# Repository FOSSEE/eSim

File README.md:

<h1 align="center">eSim — Electronic Circuit Simulation</h1>

<p align="center">
  <strong>An Open-Source EDA Tool for Circuit Design, Simulation, Analysis & PCB Design</strong><br/>
  <em>Developed by <a href="https://www.fossee.in/">FOSSEE Team</a> at <a href="https://www.iitb.ac.in/">IIT Bombay</a></em>
</p>

<p align="center">

</p>

<p align="center">

</p>

<p align="center">
  <a href="#-features">Features</a> •
  <a href="#%EF%B8%8F-architecture">Architecture</a> •
  <a href="#-installation">Installation</a> •
  <a href="#-project-structure">Project Structure</a> •
  <a href="#-tech-stack">Tech Stack</a> •
  <a href="#-contributing">Contributing</a> •
  <a href="#-license">License</a>
</p>

---

## 📖 About

**eSim** is a free and open-source EDA (Electronic Design Automation) tool for circuit design, simulation, analysis, and PCB design. It is an integrated tool built using open-source software such as **KiCad**, **Ngspice**, **GHDL**, and **Makerchip**, providing a seamless workflow from schematic capture to simulation results.

eSim is designed for electronics engineers, students, educators, and hobbyists who want a powerful yet cost-free alternative to proprietary EDA tools. It supports analog, digital, and **mixed-signal simulations**, including microcontroller integration.

<p align="center">
  <b>📥 Download:</b> <a href="https://esim.fossee.in/downloads">v2.5 Release</a> &nbsp;&nbsp;|&nbsp;&nbsp; 
  <b>📄 Manual:</b> <a href="https://static.fossee.in/esim/manuals/eSim_Manual_2.5.pdf">PDF Guide</a> &nbsp;&nbsp;|&nbsp;&nbsp; 
  <b>📚 Docs:</b> <a href="https://esim.readthedocs.io/en/latest/">ReadTheDocs</a>
</p>

---

## ✨ Features

| Category | Feature | Description |
|:---------|:--------|:------------|
| • **Design** | Schematic Capture | Draw circuit schematics using KiCad's schematic editor with eSim's custom symbol libraries |
| • **Conversion** | KiCad to Ngspice | Convert KiCad schematics to Ngspice-compatible netlists for simulation |
| • **Simulation** | Ngspice Engine | Run DC, AC, Transient, and other SPICE analyses with real-time interactive plots |
| • **Analysis** | Waveform Plotting | Visualize simulation results with matplotlib-based Python plots and Ngspice native plots |
| • **Model Editor** | Device Models | Create and edit SPICE device models (Diodes, BJTs, MOSFETs, JFETs, IGBTs, etc.) |
| • **Subcircuits** | Subcircuit Builder | Build, manage, and upload reusable subcircuit blocks |
| • **Mixed-Signal** | NGHDL Integration | Interface VHDL digital models (via GHDL) with analog Ngspice simulations |
| • **Verilog** | Makerchip + NgVeri | Use Makerchip IDE for Verilog/TL-Verilog design and convert to Ngspice models |
| • **PCB** | Layout Design | Design PCB layouts using KiCad's PCB editor with eSim's footprint libraries |
| • **Converters** | Schematic Import | Convert PSpice and LTSpice schematics/libraries to KiCad-compatible formats |
| • **Modelica** | Ngspice-to-Modelica | Convert Ngspice netlists to Modelica models for OpenModelica simulation |
| • **SKY130 PDK** | SkyWater 130nm | Support for SkyWater SKY130 open-source Process Design Kit |
| • **IHP PDK** | IHP OpenPDK | Integration with IHP SG13G2 open-source PDK for SiGe BiCMOS |
| • **OpenROAD** | Netlist-to-ASIC | Automated digital ASIC design (Synthesis, placement, routing, layout generation) from Verilog RTL to GDSII layout|

---

## 🏗️ Architecture

### High-Level System Architecture

```mermaid
graph TB
    %% Styling
    classDef ui fill:#2A3F54,stroke:#1ABB9C,stroke-width:2px,color:#fff
    classDef core fill:#3E536C,stroke:#3498DB,stroke-width:2px,color:#fff
    classDef engine fill:#1F2D3D,stroke:#E74C3C,stroke-width:2px,color:#fff
    classDef data fill:#E9F0F5,stroke:#95A5A6,stroke-width:1px,color:#333
    
    subgraph UI ["User Interface (PyQt6)"]
        A[Application Main Window]:::ui
        PE[Project Explorer]:::ui
        DA[Dock Area Workspace]:::ui
        TE[Time Explorer]:::ui
        CON[Console Widget]:::ui
        
        A --> PE & DA & TE & CON
    end

    subgraph CORE ["Core Python Modules"]
        K2N[KiCad-to-Ngspice]:::core
        SIM[Ngspice Simulator]:::core
        PLT[Matplotlib Plotter]:::core
        ME[Model Editor]:::core
        SC[Subcircuit Builder]:::core
        
        DA --> K2N & SIM & ME & SC
    end

    subgraph INTEGRATION ["Mixed-Signal & External APIs"]
        NGHDL[NGHDL Interface]:::core
        MKR[Makerchip/NgVeri]:::core
        MOD[Modelica Converter]:::core
        CONV[PSpice/LTSpice Converter]:::core
        
        DA --> NGHDL & MKR & MOD & CONV
    end

    subgraph ENGINES ["Simulation & EDA Engines"]
        KICAD[KiCad Eeschema]:::engine
        PCB[KiCad Pcbnew]:::engine
        NGSPICE[Ngspice Backend]:::engine
        GHDL[GHDL Simulator]:::engine
        VER[Verilator]:::engine
        OM[OpenModelica]:::engine
    end

    %% Data Flow
    XML[(Netlist / XML)]:::data
    RAW[(Raw Data / txt)]:::data
    VHDL[(VHDL Files)]:::data
    
    K2N -- Generates --> XML
    XML -- Consumed by --> NGSPICE
    SIM -- Triggers --> NGSPICE
    NGSPICE -- Outputs --> RAW
    RAW -- Parsed by --> PLT
    
    NGHDL -- Compiles --> VHDL
    VHDL -- Simulated by --> GHDL
    GHDL -- Co-simulates --> NGSPICE
    
    MKR -- Verilog/TL-V --> VER
    
    KICAD -- Schematic --> K2N
    KICAD -- Netlist --> PCB
```

*For detailed simulation workflows, sub-system operations, and system flowcharts, please refer to our [Architecture & Workflows Guide](ARCHITECTURE.md).*

---

## 📂 Project Structure

### Root Directory

| Path | Type | Description |
|:-----|:-----|:------------|
| `src/` | 📁 Directory | **Core application source code** — all Python modules for the eSim GUI and backend |
| `library/` | 📁 Directory | **Component libraries** — device models, KiCad symbols, subcircuits, and PDK data |
| `nghdl/` | 📁 Directory | **NGHDL module** — Ngspice-GHDL interface for mixed-signal VHDL simulation |
| `Examples/` | 📁 Directory | **42 example projects** — ready-to-simulate circuits (RC, BJT, Op-Amp, Mixed-Signal, etc.) |
| `images/` | 📁 Directory | **UI assets** — application icons, toolbar images, logos, and splash screen |
| `scripts/` | 📁 Directory | **Launch & setup scripts** — shell scripts for Linux installation and launching |
| `docs/` | 📁 Directory | **Sphinx documentation** — RST files for ReadTheDocs auto-generated developer docs |
| `code/` | 📁 Directory | **Sphinx autodoc config** — mirrors `src/` structure for API documentation generation |
| `flatpak/` | 📁 Directory | **Flatpak packaging** — manifest and wrapper scripts for universal Linux distribution |
| `appimage/` | 📁 Directory | **AppImage packaging** — build scripts for portable Linux AppImage bundles |
| `docker-launcher/` | 📁 Directory | **Docker support** — Dockerfile, launcher script, and CI workflows for containerized builds |
| `snap/` | 📁 Directory | **Snap packaging** — `snapcraft.yaml` for building Snap packages |
| `ihp/` | 📁 Directory | **IHP PDK integration** — install script for IHP SG13G2 open-source SiGe BiCMOS PDK |
| `orfs/` | 📁 Directory | **OpenROAD integration** — install & setup scripts for ORFS (RTL-to-GDSII ASIC design & layout) |
| `patches/` | 📁 Directory | **Source patches** — patch files for modifying Ngspice/GHDL behavior in sandboxed environments |
| `.github/` | 📁 Directory | **GitHub config** — issue templates, PR templates, and CI/CD workflow definitions |
| `setup.py` | 📄 File | Python package configuration for pip installation |
| `requirements.txt` | 📄 File | Python dependency list (PyQt6, matplotlib, numpy, scipy, etc.) |
| `conf.py` | 📄 File | Sphinx documentation configuration |
| `VERSION` | 📄 File | Current version identifier (`2.5`) |
| `INSTALL` | 📄 File | Detailed multi-platform installation instructions |
| `LICENSE` | 📄 File | GNU General Public License v3.0 |

### Source Code (`src/`) — Detailed Module Breakdown

```
src/
├── frontEnd/               # GUI & Main Application
│   ├── Application.py      # Main window, toolbar setup, menu actions (960 lines)
│   ├── DockArea.py          # Tabbed dock workspace for editors/simulators (24K)
│   ├── ProjectExplorer.py   # File tree browser for project navigation (20K)
│   ├── TimeExplorer.py      # Project snapshot/version management (8K)
│   ├── TerminalUi.py        # Embedded terminal widget (5K)
│   └── Workspace.py         # Workspace selection dialog (6K)
│
├── kicadtoNgspice/          # KiCad-to-Ngspice Conversion Engine
│   ├── KicadtoNgspice.py    # Main conversion controller & UI (41K)
│   ├── Convert.py           # Netlist parsing and SPICE generation (40K)
│   ├── Analysis.py          # Analysis type configuration (DC, AC, Transient) (32K)
│   ├── DeviceModel.py       # Device model parameter handling (56K)
│   ├── Source.py             # Source component configuration (15K)
│   ├── Processing.py         # Netlist processing pipeline (26K)
│   ├── SubcircuitTab.py      # Subcircuit selection in converter (9K)
│   ├── Microcontroller.py    # Microcontroller model support (10K)
│   ├── Model.py              # Model file handling (6K)
│   └── TrackWidget.py        # UI tracking widget (1K)
│
├── ngspiceSimulation/       # Simulation Engine & Plotting
│   ├── NgspiceWidget.py     # Ngspice process management & execution (16K)
│   ├── plot_window.py       # matplotlib-based waveform plotter (66K)
│   ├── plotting_widgets.py  # Custom plot controls and widgets (8K)
│   └── data_extraction.py   # Simulation data file parser (11K)
│
├── modelEditor/             # SPICE Model Editor
│   └── ModelEditor.py       # GUI for creating/editing device models (33K)
│
├── subcircuit/              # Subcircuit Management
│   ├── Subcircuit.py        # Subcircuit manager main window (3K)
│   ├── newSub.py            # Create new subcircuit (3K)
│   ├── openSub.py           # Open existing subcircuit (1K)
│   ├── uploadSub.py         # Upload subcircuit to library (4K)
│   └── convertSub.py        # Subcircuit format conversion (2K)
│
├── maker/                   # Makerchip & NgVeri Integration
│   ├── Maker.py             # Makerchip IDE integration (23K)
│   ├── NgVeri.py            # Verilog-to-Ngspice model generator (17K)
│   ├── ModelGeneration.py   # Auto model generation pipeline (48K)
│   ├── createkicad.py       # KiCad symbol creation for models (14K)
│   ├── makerchip.py         # Makerchip cloud IDE connector (3K)
│   ├── netlist2rtl.py       # Netlist-to-Verilog conveter (4K)
│   ├── orfs.py              # eSim to ORFS connnector (7K)
│   └── Appconfig.py         # Maker-specific configuration (2K)
│
├── converter/               # Schematic Format Converters
│   ├── pspiceToKicad.py     # PSpice schematic importer (5K)
│   ├── ltspiceToKicad.py    # LTSpice schematic importer (6K)
│   ├── libConverter.py      # Library format converter (3K)
│   ├── LtspiceLibConverter.py # LTSpice library converter (4K)
│   ├── browseSchematic.py   # File browser for schematics (550B)
│   ├── LTSpiceToKiCadConverter/ # LTSpice conversion engine
│   └── schematic_converters/    # Additional schematic parsers
│
├── ngspicetoModelica/       # 📐 Ngspice-to-Modelica Converter
│   ├── NgspicetoModelica.py # Core conversion engine (54K)
│   └── ModelicaUI.py        # Modelica converter GUI (10K)
│
├── configuration/           # ⚙️ Application Configuration
│   └── Appconfig.py         # Global config, paths, process tracking (4K)
│
├── projManagement/          # 📋 Project Management
│   ├── Kicad.py             # KiCad integration (launch schematic/PCB editor) (9K)
│   ├── Validation.py        # Tool and file validation utilities (7K)
│   ├── Worker.py            # Background process/thread management (3K)
│   ├── newProject.py        # New project creation logic (5K)
│   └── openProject.py       # Open existing project logic (3K)
│
└── browser/                 # 📖 Help & Documentation
    ├── Welcome.py           # Welcome screen display (941B)
    └── UserManual.py        # User manual viewer (731B)
```

### Library Directory (`library/`) — Component Libraries

| Path | Description |
|:-----|:------------|
| `deviceModelLibrary/` | SPICE device models organized by type: Diode, BJT (Transistor), MOSFET (MOS), JFET, IGBT, LEDs, Switches, Transmission Lines, and user libraries |
| `kicadLibrary/` | KiCad schematic symbols (`eSim-symbols/`), footprint libraries (`kicad_eSim-Library/`), and project templates |
| `SubcircuitLibrary/` | Reusable subcircuit definitions for common circuit blocks |
| `modelParamXML/` | XML parameter definitions for device model editor forms |
| `ngspicetoModelica/` | Mapping files for Ngspice-to-Modelica component translation |
| `browser/` | HTML/resource files for the built-in help browser |
| `orfs/` | KLayout binaries & libraries (klayout-0.30.7) required for OpenROAD/ASIC layout visualization |
| `tlv/` | TL-Verilog support files for Makerchip integration |

### NGHDL Module (`nghdl/`) — Mixed-Signal Interface

| Path | Description |
|:-----|:------------|
| `src/ngspice_ghdl.py` | Core interface: manages VHDL upload, GHDL compilation, and Ngspice code model creation |
| `src/model_generation.py` | Generates C code models from VHDL port definitions for Ngspice |
| `src/createKicadLibrary.py` | Auto-generates KiCad symbols from VHDL entity definitions |
| `src/ghdlserver/` | GHDL foreign interface server for inter-process communication with Ngspice |
| `install-nghdl.sh` | Automated installer for NGHDL dependencies (GHDL, Verilator, Ngspice) |
| `Example/` | Example VHDL models and mixed-signal simulation projects |

---

## 🛠️ Tech Stack

| Layer | Technology | Purpose |
|:------|:-----------|:--------|
| **Language** |  | Core application logic |
| **GUI Framework** |  | Desktop GUI (windows, dialogs, toolbars, docks) |
| **Plotting** |  | Waveform visualization and data plotting |
| **Numerics** |   | Numerical computation and signal processing |
| **Schematic & PCB** |  | Schematic capture and PCB layout design |
| **SPICE Simulation** |  | Analog/mixed-signal circuit simulation engine |
| **VHDL Simulation** |  | VHDL analysis, compilation, and simulation |
| **Verilog** |  | Verilog HDL simulation and model generation |
| **HDL Cloud IDE** |  | Online Verilog/TL-Verilog IDE integration |
| **Modelica** |  | Multi-domain modeling and simulation |
| **PDK** |  | SkyWater 130nm open-source process design kit |
| **Packaging** |   | Cross-distribution Linux packaging & containers |
| **Documentation** |   | Auto-generated developer documentation |
| **CI/CD** |  | Automated builds, Docker images, and releases |

### Key Python Dependencies

| Package | Version | Purpose |
|:--------|:--------|:--------|
| `PyQt6` | ≥ 6.5.0 | GUI framework |
| `matplotlib` | 3.7.5 | Waveform plotting |
| `numpy` | 1.24.4 | Numerical computation |
| `scipy` | 1.10.1 | Scientific computing |
| `pillow` | 12.2.0 | Image processing |
| `hdlparse` | 1.0.4 | HDL file parsing |
| `watchdog` | 4.0.2 | File system monitoring |
| `pyparsing` | 3.1.4 | Parser building toolkit |

---

## 💻 Installation

### Supported Platforms

| Platform | Method | Status |
|:---------|:-------|:------:|
| **All Linux** (Fedora, Ubuntu, openSUSE, Arch, etc.) | Flatpak | ✅ Recommended |
| **Ubuntu** 22.04 / 23.04 / 24.04 LTS | Native Installer | ✅ Supported |
| **Windows** 8 / 10 / 11 | Windows Installer | ✅ Supported |
| **Docker** (any OS) | Docker Container | ✅ Supported |

### 🐧 Linux — Flatpak (Recommended for all distributions)

```bash
# 1. Install Flatpak (if not already installed)
# Fedora:    sudo dnf install flatpak
# Ubuntu:    sudo apt install flatpak
# openSUSE:  sudo zypper install flatpak
# Arch:      sudo pacman -S flatpak

# 2. Add Flathub repository
flatpak remote-add --if-not-exists flathub https://dl.flathub.org/repo/flathub.flatpakrepo

# 3. Install eSim
flatpak install flathub org.fossee.eSim

# 4. Run eSim
flatpak run org.fossee.eSim
```

> **⚠️ Flatpak Limitations:** NGHDL, Makerchip, and SKY130 PDK are not included in the Flatpak build. For full mixed-signal support, use the Ubuntu native installer.

### 🐧 Ubuntu — Native Installer

```bash
# 1. Download and extract eSim
unzip eSim-2.5.zip
cd eSim-2.5

# 2. Install eSim with all dependencies
chmod +x install-eSim.sh
./install-eSim.sh --install

# 3. Run eSim
esim
# Or double-click the eSim desktop icon
```

### 🪟 Windows

1. Download the eSim installer from [esim.fossee.in/downloads](https://esim.fossee.in/downloads)
2. Disable antivirus temporarily (if required)
3. **Important:** Remove MinGW/MSYS from the PATH environment variable if previously installed
4. Run the installer and follow the on-screen instructions
5. Launch eSim from the Start Menu or desktop shortcut

### 🐋 Docker

Refer to the [Docker Launcher README](docker-launcher/README.md) for instructions on running eSim in a containerized environment.

### 📦 Build from Source (Flatpak)

```bash
cd eSim
flatpak-builder build flatpak/org.fossee.eSim.yml --install --user
```

> 📖 For comprehensive installation instructions, see the [INSTALL](INSTALL) file.

---

## 🔄 CI/CD & Packaging

| Workflow | File | Purpose |
|:---------|:-----|:--------|
| Docker Image Build | `.github/workflows/docker-image.yml` | Builds and publishes the eSim Docker image |
| Docker Launcher Build | `.github/workflows/docker-launcher-build.yml` | Builds the cross-platform Python launcher |
| Ubuntu Release | `.github/workflows/release_ubuntu.yml` | Automated Ubuntu `.deb` package builds |

| Packaging Format | Directory | Description |
|:-----------------|:----------|:------------|
| Flatpak | `flatpak/` | Universal Linux package via Flathub |
| AppImage | `appimage/` | Portable single-file Linux executable |
| Snap | `snap/` | Ubuntu Snap Store package |
| Docker | `docker-launcher/` | Containerized distribution with GUI forwarding |

---

## 📋 Example Projects

eSim ships with **42 ready-to-simulate example projects** in the `Examples/` directory:

<details>
<summary><b>📂 Click to expand full example list</b></summary>

| # | Category | Example | Description |
|:-:|:---------|:--------|:------------|
| 1 | 🔌 Basic | `RC` | RC circuit transient analysis |
| 2 | 🔌 Basic | `RL` | RL circuit transient analysis |
| 3 | 🔌 Basic | `RLC` | RLC circuit resonance analysis |
| 4 | 🔌 Basic | `Series_Resonance` | Series RLC resonance |
| 5 | 🔌 Basic | `Parallel_Resonance` | Parallel RLC resonance |
| 6 | 💡 Diodes | `Diode_characteristics` | Diode I-V characteristics |
| 7 | 💡 Diodes | `Halfwave_Rectifier` | Half-wave rectifier circuit |
| 8 | 💡 Diodes | `Fullwavebridgerectifier` | Full-wave bridge rectifier |
| 9 | 💡 Diodes | `Clippercircuit` | Diode clipper circuit |
| 10 | 💡 Diodes | `Clampercircuit` | Diode clamper circuit |
| 11 | 💡 Diodes | `Zener_Characteristic` | Zener diode characteristics |
| 12 | 🔋 BJT | `BJT_CE_config` | BJT common-emitter configuration |
| 13 | 🔋 BJT | `BJT_CB_config` | BJT common-base configuration |
| 14 | 🔋 BJT | `BJT_amplifier` | BJT amplifier circuit |
| 15 | 🔋 BJT | `BJT_Biascircuit` | BJT bias circuit design |
| 16 | 🔋 BJT | `BJT_Frequency_Response` | BJT frequency response analysis |
| 17 | 📟 FET | `FET_Characteristic` | FET output characteristics |
| 18 | 📟 FET | `FET_Amplifier` | FET amplifier circuit |
| 19 | 📟 FET | `FrequencyResponse_JFET` | JFET frequency response |
| 20 | 🎛️ Op-Amp | `InvertingAmplifier` | Op-amp inverting amplifier (LM741) |
| 21 | 🎛️ Op-Amp | `Differentiator` | Op-amp differentiator circuit |
| 22 | 🎛️ Op-Amp | `Integrator_LM_741` | Op-amp integrator |
| 23 | 🎛️ Op-Amp | `Precision_Rectifiers_using_LM741` | Precision rectifier circuits |
| 24 | 🔲 Digital | `BasicGates` | Basic logic gates |
| 25 | 🔲 Digital | `Half_Adder` | Half-adder circuit |
| 26 | 🔲 Digital | `FullAdder` | Full-adder circuit |
| 27 | 🔲 Digital | `JK_Flipflop` | JK flip-flop circuit |
| 28 | 🔲 Digital | `4_bit_JK_ff` | 4-bit JK flip-flop counter |
| 29 | 🔲 Digital | `CMOS_NAND_Gate` | CMOS NAND gate |
| 30 | 🔲 Digital | `Analysis_Of_Digital_IC` | Digital IC analysis |
| 31 | ⏱️ Timers | `Astable555` | 555 timer astable mode |
| 32 | ⏱️ Timers | `Monostable555` | 555 timer monostable mode |
| 33 | 🔁 SCR | `HalfwaveRectifier_SCR` | SCR half-wave rectifier |
| 34 | 🔁 SCR | `FullwaveRectifier_SCR` | SCR full-wave rectifier |
| 35 | 📡 Filters | `High_Pass_Filter` | High-pass filter design |
| 36 | 📡 Filters | `Low_Pass_Filter` | Low-pass filter design |
| 37 | ⚡ Regulators | `7805VoltageRegulator` | 7805 voltage regulator |
| 38 | ⚡ Regulators | `7812VoltageRegulator` | 7812 voltage regulator |
| 39 | 🌀 Oscillators | `UJT_Relaxation_Oscillator` | UJT relaxation oscillator |
| 40 | 🌀 Oscillators | `Phase_Locked_Loop` | PLL circuit |
| 41 | 🔀 Mixed-Signal | `Mixed_Signal` | Mixed analog-digital simulation (NGHDL) |
| 42 | 🔌 Power | `Transformer` | Transformer circuit analysis |

</details>

---

## 🤝 Contributing

We welcome contributions from the community! Whether it's bug fixes, new features, documentation improvements, or example circuits — every contribution matters.

### How to Contribute

```mermaid
flowchart LR
    A["🍴 Fork<br/>Repository"] --> B["🌿 Create<br/>Branch"]
    B --> C["💻 Make<br/>Changes"]
    C --> D["✅ Commit &<br/>Push"]
    D --> E["📬 Open<br/>Pull Request"]

    style A fill:#6c5ce7,color:#fff
    style B fill:#00b894,color:#fff
    style C fill:#0984e3,color:#fff
    style D fill:#fdcb6e,color:#333
    style E fill:#e17055,color:#fff
```

1. **Fork** the repository to your GitHub account
2. **Clone** your fork:
   ```bash
   git clone https://github.com/<your-username>/eSim.git
   ```
3. **Create a new branch** for your changes:
   ```bash
   git checkout -b feature/your-feature-name
   ```
4. **Make your changes** and commit with a descriptive message:
   ```bash
   git add <files>
   git commit -m "Fixes issue #<number> - Brief description of changes"
   ```
5. **Push** to your fork and **open a Pull Request**:
   ```bash
   git push origin feature/your-feature-name
   ```

> **📌 Guidelines:**
> - Each PR should reference an existing issue
> - One commit per pull request (squash if needed)
> - Follow [PEP 8](https://www.python.org/dev/peps/pep-0008/) code style
> - Include a commit body describing what you changed and why

For detailed contribution guidelines, see [CONTRIBUTING.md](CONTRIBUTING.md).

---

## 👥 Contributors

A huge thank you to all **149+ amazing people** who have contributed to eSim! 🎉

<table align="center" style="border:none;">
  <tr>
    <td align="center" width="250" style="border:none;">
      <a href="https://github.com/Eyantra698Sumanto" style="text-decoration:none;">
        <br/>
        <b>🥇 Sumanto Kar</b>
      </a><br/>
      <sub>Lead Maintainer · 320 commits</sub>
    </td>
    <td align="center" width="250" style="border:none;">
      <a href="https://github.com/rahulp13" style="text-decoration:none;">
        <br/>
        <b>🥈 Rahul Paknikar</b>
      </a><br/>
      <sub>265 commits</sub>
    </td>
    <td align="center" width="250" style="border:none;">
      <a href="https://github.com/fahim-oscad" style="text-decoration:none;">
        <br/>
        <b>🥉 Fahim Khan</b>
      </a><br/>
      <sub>244 commits</sub>
    </td>
  </tr>
</table>

<p align="center">
  
</p>

<p align="center"><em>149+ contributors and counting! <a href="https://github.com/fossee/esim/graphs/contributors">View all contributors →</a></em></p>

---

## 📞 Contact & Support

| Channel | Link |
|:--------|:-----|
| 📧 **Email** | [contact-esim@fossee.in](mailto:contact-esim@fossee.in) |
| 🌐 **Website** | [esim.fossee.in](https://esim.fossee.in/) |
| 💬 **Forum** | [forums.fossee.in](https://forums.fossee.in/) |
| 📞 **Contact Page** | [esim.fossee.in/contact-us](https://esim.fossee.in/contact-us) |
| 📄 **User Manual** | [eSim Manual v2.5 (PDF)](https://static.fossee.in/esim/manuals/eSim_Manual_2.5.pdf) |
| 📚 **Developer Docs** | [esim.readthedocs.io](https://esim.readthedocs.io/en/latest/) |

---

<p align="center">
  <strong>Built with ❤️ by the <a href="https://www.fossee.in/">FOSSEE Team</a> at <a href="https://www.iitb.ac.in/">IIT Bombay</a></strong>
</p>

<p align="center">
  
  &nbsp;&nbsp;&nbsp;&nbsp;
  
</p>

<p align="center">
  <sub>⭐ If you find eSim useful, consider giving it a star on GitHub!</sub>
</p>

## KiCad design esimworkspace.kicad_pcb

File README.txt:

# REF01 Precision Voltage Reference

REF01 is an 8-pin precision voltage reference IC. It provides a stable 10.0 V reference output with excellent temperature stability, low noise, and high accuracy. The output voltage can be adjusted by approximately ±3% using an external trim resistor. It is widely used in precision analog and measurement applications. :contentReference[oaicite:0]{index=0}

## Usage/Examples

Precision Data Acquisition Systems

Analog-to-Digital Converters (ADC)

Digital-to-Analog Converters (DAC)

Industrial Process Control

Precision Test and Measurement Instruments

Reference Voltage Sources

## Documentation

To know the details of REF01 IC please go through the documentation : https://www.analog.com/media/en/technical-documentation/data-sheets/REF01_02_03.pdf :contentReference[oaicite:1]{index=1}

## Comments/Notes

Please note this is a precision voltage reference IC intended for applications requiring a highly stable reference voltage. The device operates from an input supply of 12 V to 36 V and provides a fixed 10 V output with up to 10 mA load current. Proper supply bypassing and PCB layout are recommended to achieve optimum noise performance and stability. :contentReference[oaicite:2]{index=2}

## Contributer

Name: *Sanchi Ramteke*  
Email: *sanchiramteke2008@gmail.com*  
Year: 2026  
Position: Contributor

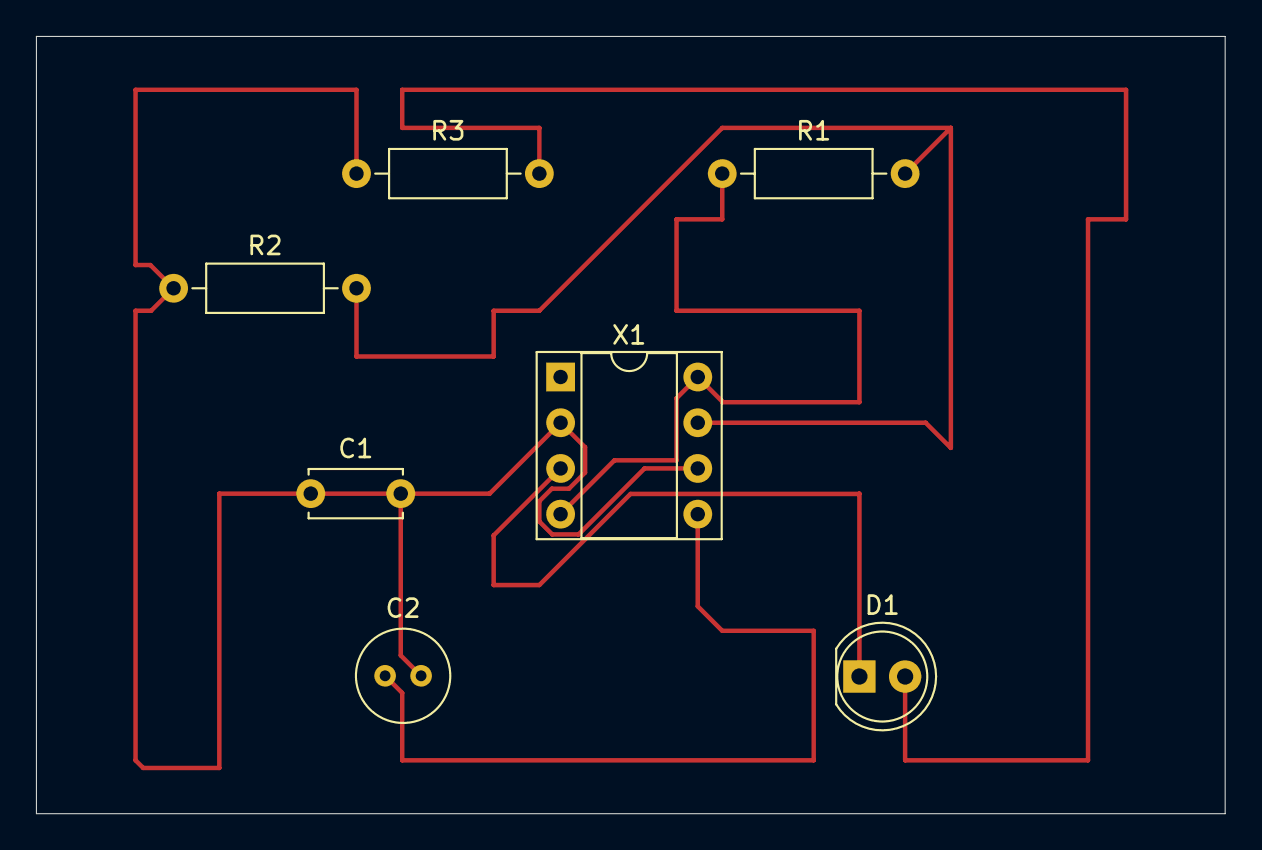
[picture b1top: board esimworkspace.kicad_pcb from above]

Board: 2 copper layers, 66.0 x 43.2 mm, 7 parts (0 on the bottom side), 6 nets.

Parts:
C1: capacitor; C_Disc_D5.0mm_W2.5mm_P5.00mm
C2: capacitor; C_Radial_D5.0mm_H7.0mm_P2.00mm
D1: LED; LED_D5.0mm
R1, R2, R3: resistor; R_Axial_DIN0207_L6.3mm_D2.5mm_P10.16mm_Horizontal
X1: NE555; DIP-8_W7.62mm_Socket

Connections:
GND: C1.1, C1.2, C2.2, R2.1, R3.1, X1.2 (TRIG), X1.6 (THRS)
unnamed: C2.1, X1.5 (CV)
unnamed: D1.1 (+), X1.3 (OUT)
unnamed: D1.2 (-), R3.2
unnamed: R1.1, X1.4 (RST), X1.8 (Vcc)
unnamed: R1.2, R2.2, X1.7 (DIS)

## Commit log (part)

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2026-06-13 SNx4HC03 is Quad 2-input NAND gate IC.
2026-06-13 SNx5452B is AND-OR-Invert gate IC.
2026-06-13 fix: replace exec_() with exec() in Chatbot.py for PyQt6 compatibility
2026-06-14 refactor(ui): embed individual tool manager into main tab
2026-06-14 fix(ui): remove redundant button linking to deleted function
2026-06-14 feat(ui): implement three-tab layout for individual tool manager
2026-06-14 refactor(ui): streamline interface constraints and restore minimal layout structure
2026-06-15 refactor: move platform-specific code to platform_util.py
2026-06-15 Fixed the missing PYTHON variable from gui_fixed.py
2026-06-16 fix: migrate frontEnd enums to PyQt6 and add standalone chatbot launcher for chatbot testing
2026-06-16 fix: fix remaining QTextCursor PyQt5 enums restored by merge conflict
2026-06-16 Some more refactoring
2026-06-17 cleanup(toolManager): delete dead shell scripts and orphaned bytecode
    check-packages-final.sh and update-dependency-final.sh had zero
    references in the entire repository — completely dead code.
    Deleted 4 orphaned .pyc files from __pycache__ that had no
    corresponding .py source (covered by existing *.pyc gitignore).
2026-06-17 feat(toolManager): create pm_platform.py — unified OS detection, subprocess, admin helpers
2026-06-17 refactor(toolManager): modular architecture with backends/ package, worker, and unified registry
    Break the 1434-line tool_manager_windows.py monolith into a clean
    backends/ package with adapter pattern for backward compatibility.
    === backends/ package (Phase 5) ===
    - base.py — Backend(ABC) with find_executable, install_package,
    download_file, extract_7z, run_installer, and shared run_cmd/which
    - windows/ — WindowsBackend wrapping Chocolatey (choco.py),
2026-06-18 feat: automate headless Ollama startup and model pulling
2026-06-19 feat(toolManager): LinuxBackend with package manager abstraction and tool file Linux branches
    Phase 6 & 7 — complete Linux backend infrastructure and cleanup:
    - backends/linux/ package (replaces flat linux.py):
    - pm.py — abstraction for apt, dnf, pacman, zypper, pkg, xbps
    - search.py — Linux executable discovery (PATH + /opt + snap/flatpak)
    - file_ops.py — tar, 7z, .sh/.run installer support
    - __init__.py — LinuxBackend class with run_bash_script() helper
2026-06-19 fix(toolManager): create tool_manager_linux.py CLI adapter and fix PyQt6 crash
    - Create tool_manager_linux.py — Linux CLI adapter mirroring
    tool_manager_windows.py but using LinuxBackend
    - Fix main.py lines 100 and 654 to select the correct backend
    script based on platform (linux vs windows)
    - Fix gui_fixed.py PyQt6 crash: QLineEdit.Password →
    QLineEdit.EchoMode.Password
2026-06-19 fix(linux): correct base_dir path resolution for backends/linux/ package
    When linux.py was a flat file, parent.parent resolved to toolManager/.
    After converting to a package (backends/linux/__init__.py), the path
    is one level deeper, so parent.parent.parent is needed.
2026-06-19 Add ORFS OpenROAD flow integration
2026-06-19 fix(toolManager): replace sudo password with pkexec and stream script output
    Three issues fixed:
    1. Script output now streams to GUI debug box in real time
    - run_bash_script() uses run_stream() instead of run_cmd()
    - Script stdout/stderr flows through to the CommandWorker pipe
    2. Removed manual sudo password collection (insecure, broken)
    - Deleted get_sudo_password(), self.sudo_password, needs_sudo flag
2026-06-19 fix(toolManager): cache sudo credential via sudo -S -v instead of pkexec
    Changes:
    - Remove pkexec from CommandWorker (caused 'Not authorized' errors,
    prompted for every command including check)
    - Restore sudo password prompt but only for credential caching
    - New _ensure_sudo_cache() collects password once, runs sudo -S -v
    to cache it, then discards password from memory
2026-06-19 refactor(toolManager): move sudo/lock logic into LinuxBackend, serialize bash scripts
    LinuxBackend (backends/linux/__init__.py):
    - sudo_is_cached() — check if credential is alive via sudo -n
    - ensure_sudo(password) — cache password via sudo -S -v
    - clean_package_locks() — remove stale dpkg/pacman/dnf/zypper locks
    - run_bash_script() — now serialized via threading.Lock and calls
    clean_package_locks() before every script execution, preventing
2026-06-19 Refactor platform detection and registry
2026-06-19 Enhance README with OpenROAD and ORFS details
    Added OpenROAD integration details and new files for netlist-to-ASIC design.
2026-06-19 Rename orfs-install-guide.md to README.md
2026-06-19 fix(toolManager): CLI adapter, sudo improvements, lock serialization, and path fixes
    - Add tool_manager_linux.py CLI adapter
    - Fix PyQt6 crash by inserting local path into sys.path
    - Fix base_dir path resolution for backends/linux/ package
    - Replace sudo password prompt with pkexec wrapper for GUI mode
    - Cache sudo credential via sudo -S -v instead of pkexec
    - Move sudo/lock logic (sudo_is_cached, ensure_sudo, clean_package_locks) into LinuxBackend
2026-06-19 Add deterministic netlist analysis pipeline for eSim AI Assistant
    Include:
    * netlist parsing improvements
    * circuit block detection
    * netlist summary generation
    * AI Assistant netlist understanding
    * related prompt refinements
2026-06-20 refactor(toolManager): compress 3,964 lines to 1,439 by merging tool files and deduplicating
2026-06-20 Renaming issue fixed to reduce diff noise
    Renaming fixed
2026-06-21 style(tool-manager): polish PyQt6 UI and fix dark theme inconsistencies
    This commit improves the Tool Manager UI layout and explicitly forces
    light-themed styling to fix visual bugs caused by OS-level dark mode bleeds,
    without altering any core installation or backend logic.
    UI Fixes & Improvements:
    - Wrap "Quick Setup" tab in a QScrollArea to prevent install buttons from
    being squished or hidden when the installation progress frame appears.
2026-06-21 Add deterministic NgSpice error analysis and root-cause detection pipeline
    Improve root-cause identification for NgSpice simulation failures
    - Add structured extraction of models, subcircuits and circuit facts
    - Support multiple simultaneous critical errors
    - Improve error ranking and causal relationship handling
    - Reduce hallucinated diagnostics through deterministic validation
    - Integrate analysis pipeline into chatbot workflow
2026-06-21 Added a backend file for linux and changes to the installation and uninstallation worker
2026-06-22 Move subcircuit files from SUBCKT to library/SubcircuitLibrary
2026-06-22 Add subckt file for SN74HC158
2026-06-22 Add subckt file for SN74LS139
2026-06-22 Add subckt file for MM74HC133
2026-06-22 Add subckt file for SNx4HC10
2026-06-22 Add subckt file for 74HCT280
2026-06-22 Add subckt file for SNX4HC86
2026-06-22 Add subckt file for HD74HC51
2026-06-26 Added install libreadline-dev in Dockerfile
    Added install libreadline-dev in Dockerfile
2026-06-27 Fix flatpak integration: Upgrade to PyQt6, wrap hdlparse imports, fix KiCad host spawn
2026-06-27 docs: Update README files to reflect PyQt6, hdlparse, and flatpak-spawn changes
2026-06-27 Fix AppImage build/runtime dependencies and resolve host Qt/Wayland conflicts
2026-06-28 Add installation script for ngspice latest version
    This script installs the latest version of ngspice, including necessary dependencies and configuration steps.
2026-06-28 Create .spiceinit for IHP-Open-PDK configuration
    Added a custom spiceinit file for IHP-Open-PDK with environment variable setup and simulation options.
2026-06-28 Move .spiceinit to home directory after configuration
2026-06-28 Add NMOS DC Test circuit example
